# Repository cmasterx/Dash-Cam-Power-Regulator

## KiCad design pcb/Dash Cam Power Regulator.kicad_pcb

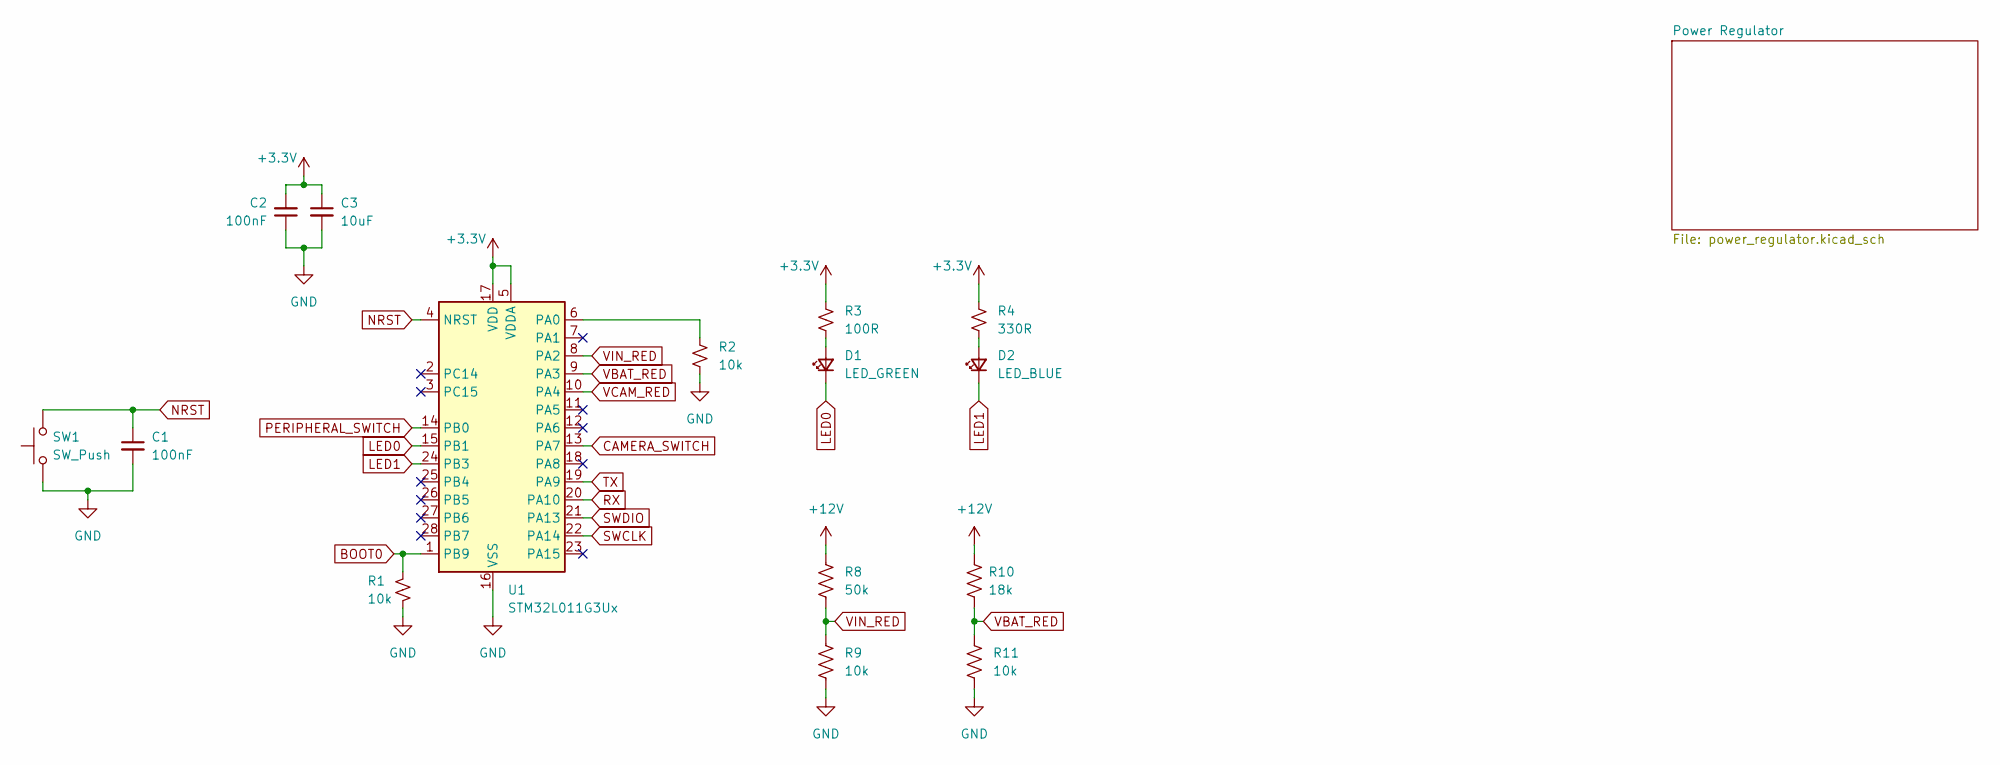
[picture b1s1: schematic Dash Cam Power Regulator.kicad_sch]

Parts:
C1, C2: 100nF; C_0603_1608Metric
C3: 10uF; C_0603_1608Metric
D1: LED_GREEN; LED_0805_2012Metric
D2: LED_BLUE; LED_0805_2012Metric
R1, R2, R9, R11: 10k; R_0402_1005Metric
R3: 100R; R_0603_1608Metric
R4: 330R; R_0603_1608Metric
R8: 50k; R_0402_1005Metric
R10: 18k; R_0402_1005Metric
SW1: SW_Push; SW_SPST_B3U-1000P
U1: STM32L011G3Ux; QFN-28_4x4mm_P0.5mm

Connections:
+3V3: C2.2, C3.1, R3.1, R4.1, U1.5 (VDDA), U1.17 (VDD); also elsewhere on the board
+12V: R8.1, R10.1; also elsewhere on the board
BOOT0: R1.1, U1.1 (PB9)
CAMERA_SWITCH: U1.13 (PA7)
GND: C1.2, C2.1, C3.2, R1.2, R2.2, R9.2, R11.2, SW1.1, U1.16 (VSS); also elsewhere on the board
LED0: D1.1 (K), U1.15 (PB1)
LED1: D2.1 (K), U1.24 (PB3)
NRST: C1.1, SW1.2, U1.4 (NRST)
unnamed: D1.2 (A), R3.2
unnamed: D2.2 (A), R4.2
unnamed: R2.1, U1.6 (PA0)
PERIPHERAL_SWITCH: U1.14 (PB0)
RX: U1.20 (PA10)
SWCLK: U1.22 (PA14)
SWDIO: U1.21 (PA13)
TX: U1.19 (PA9)
VBAT_RED: R10.2, R11.1, U1.9 (PA3)
VCAM_RED: U1.10 (PA4)
VIN_RED: R8.2, R9.1, U1.8 (PA2)

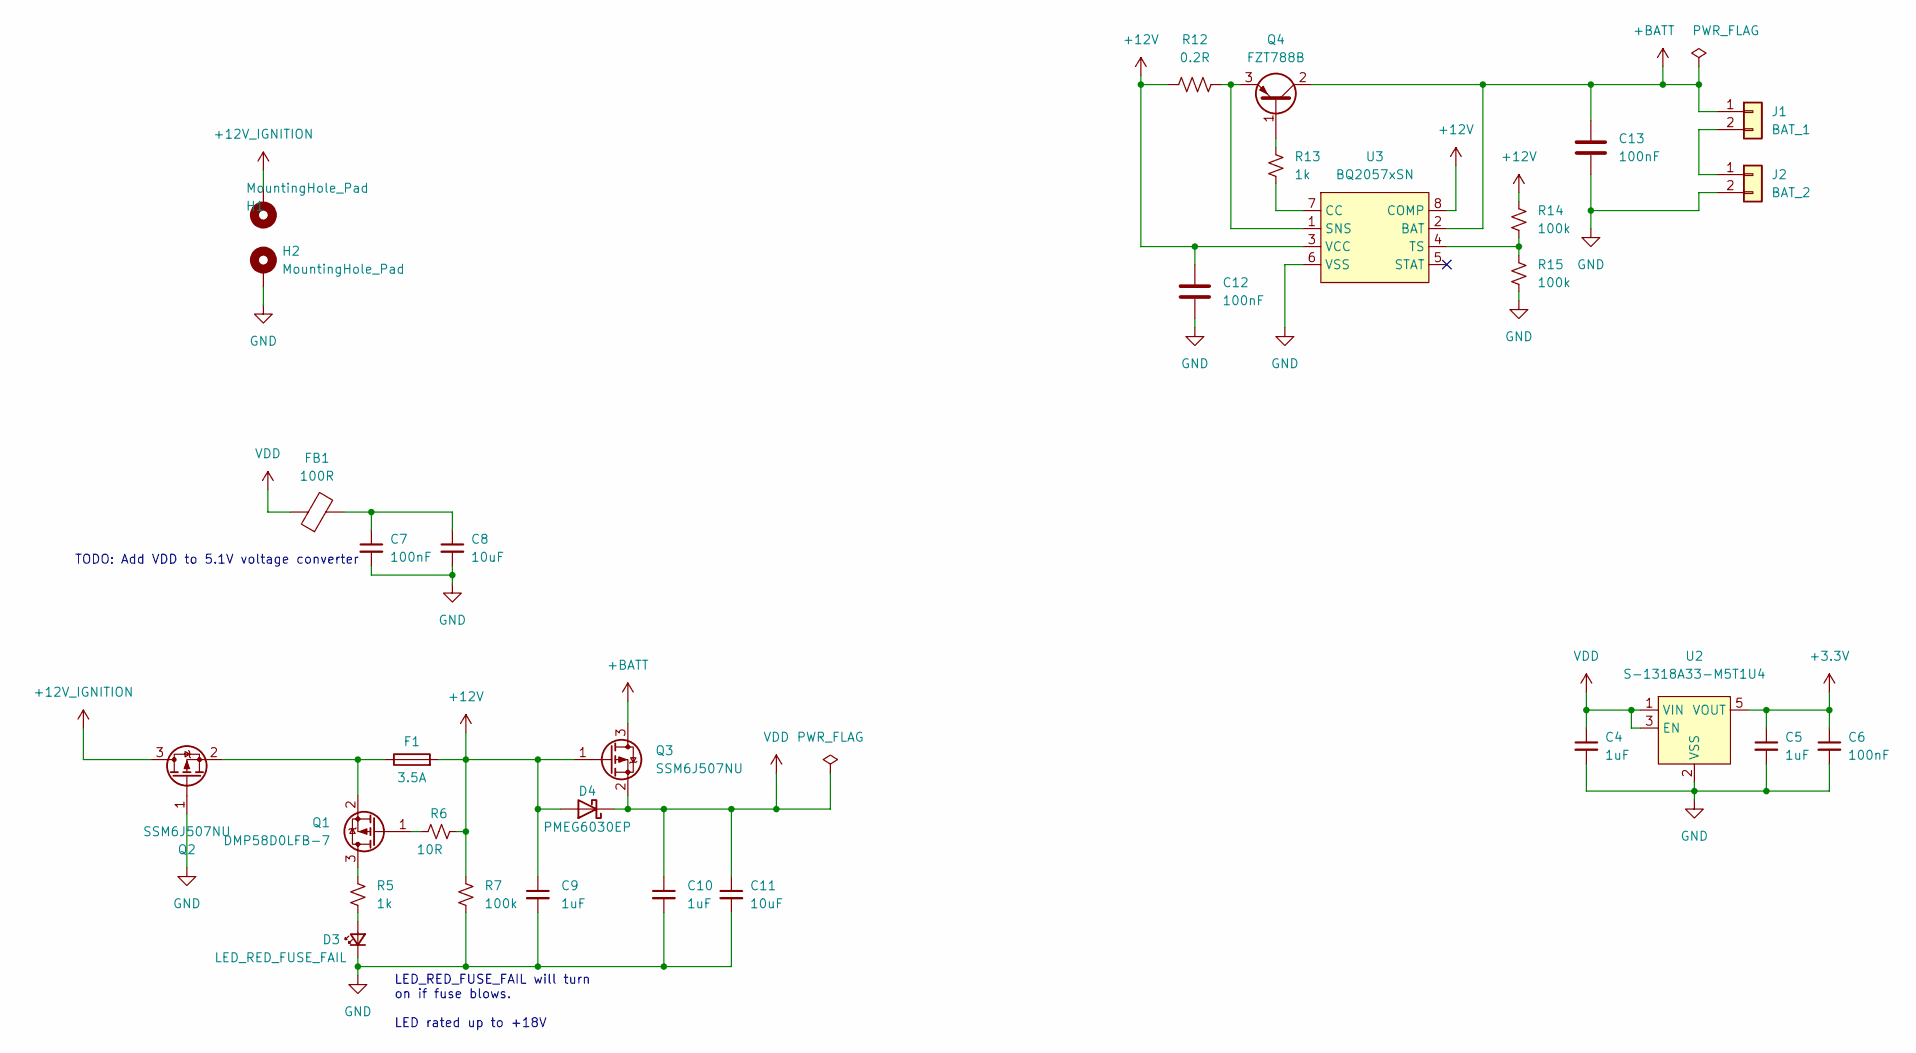
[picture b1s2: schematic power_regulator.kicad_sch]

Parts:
C4, C5, C9, C10: 1uF; C_0603_1608Metric
C6, C7, C12, C13: 100nF; C_0603_1608Metric
C8: 10uF; C_0603_1608Metric
C11: 10uF; C_0805_2012Metric
D3: LED_RED_FUSE_FAIL; LED_0603_1608Metric
D4: PMEG6030EP; D_SOD-128
F1: 3.5A; Fuseholder_Littelfuse_Nano2_154x
FB1: 100R; L_0805_2012Metric
H1, H2: MountingHole_Pad; MountingHole_3.2mm_M3_Pad_Via
J1: BAT_1; AMASS_XT30UPB-F_1x02_P5.0mm_Vertical
J2: BAT_2; AMASS_XT30UPB-F_1x02_P5.0mm_Vertical
Q1: DMP58D0LFB-7; Diodes_DFN1006-3
Q2, Q3: SSM6J507NU
Q4: FZT788B; SOT-223-3_TabPin2
R5: 1k; R_0603_1608Metric
R6: 10R; R_0402_1005Metric
R7, R14, R15: 100k; R_0402_1005Metric
R12: 0.2R; R_0805_2012Metric
R13: 1k; R_0402_1005Metric
U2: S-1318A33-M5T1U4; SOT-23-5
U3: BQ2057xSN; SOIC-8_3.9x4.9mm_P1.27mm

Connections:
+3V3: C5.1, C6.1, U2.5 (VOUT); also elsewhere on the board
+12V: C9.1, C12.1, D4.2 (A), F1.2, Q3.1 (G), R6.2, R7.1, R12.1, R14.1, U3.3 (VCC), U3.8 (COMP); also elsewhere on the board
+12V_IGNITION: H1.1, Q2.3 (D)
+BATT: C13.1, J1.1, Q3.3 (D), Q4.2 (C), U3.2 (BAT)
GND: C4.2, C5.2, C6.2, C7.2, C8.2, C9.2, C10.2, C11.2, C12.2, C13.2, D3.1 (K), H2.1, J2.2, Q2.1 (G), R7.2, R15.2, U2.2 (VSS), U3.6 (VSS); also elsewhere on the board
unnamed: C7.1, C8.1, FB1.2
unnamed: D3.2 (A), R5.2
unnamed: F1.1, Q1.2 (S), Q2.2 (S)
unnamed: J1.2, J2.1
unnamed: Q1.1 (G), R6.1
unnamed: Q1.3 (D), R5.1
unnamed: Q4.1 (B), R13.1
unnamed: Q4.3 (E), R12.2, U3.1 (SNS)
unnamed: R13.2, U3.7 (CC)
unnamed: R14.2, R15.1, U3.4 (TS)
VDD: C4.1, C10.1, C11.1, D4.1 (K), FB1.1, Q3.2 (S), U2.1 (VIN), U2.3 (EN)

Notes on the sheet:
TODO: Add VDD to 5.1V voltage converter
LED_RED_FUSE_FAIL will turn on if fuse blows. LED rated up to +18V

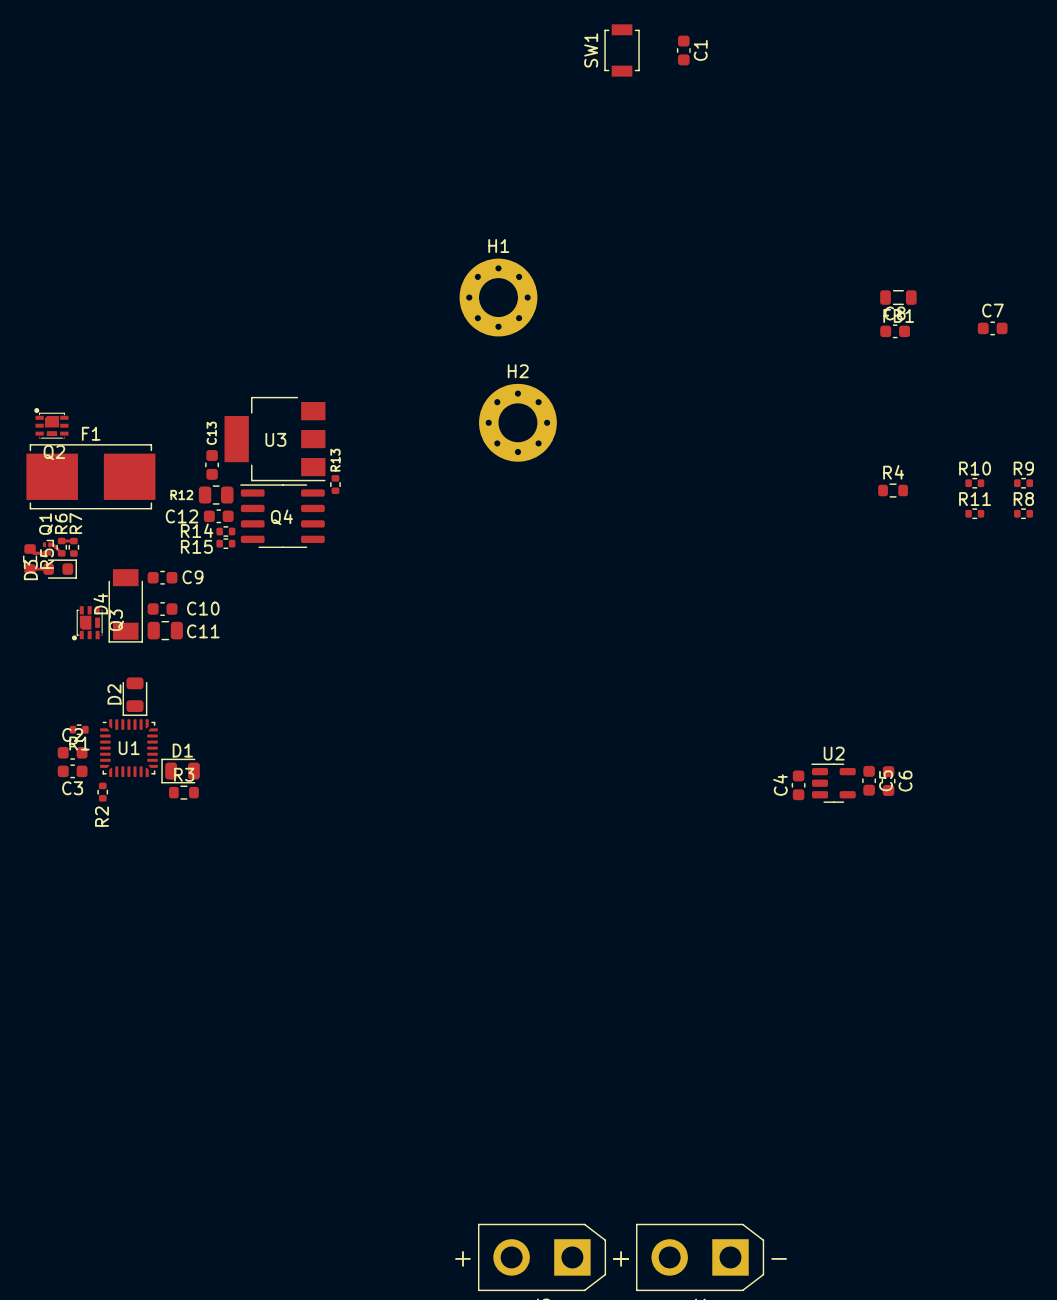
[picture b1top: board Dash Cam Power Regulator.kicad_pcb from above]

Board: 2 copper layers, 46 parts (0 on the bottom side), 25 nets.

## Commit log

2022-02-26 Add STM32CubeIDE project firmware
2022-02-26 Add .gitignore for firmware
2022-02-26 Add pcb project
2022-03-01 Add ATL KiCAD library
